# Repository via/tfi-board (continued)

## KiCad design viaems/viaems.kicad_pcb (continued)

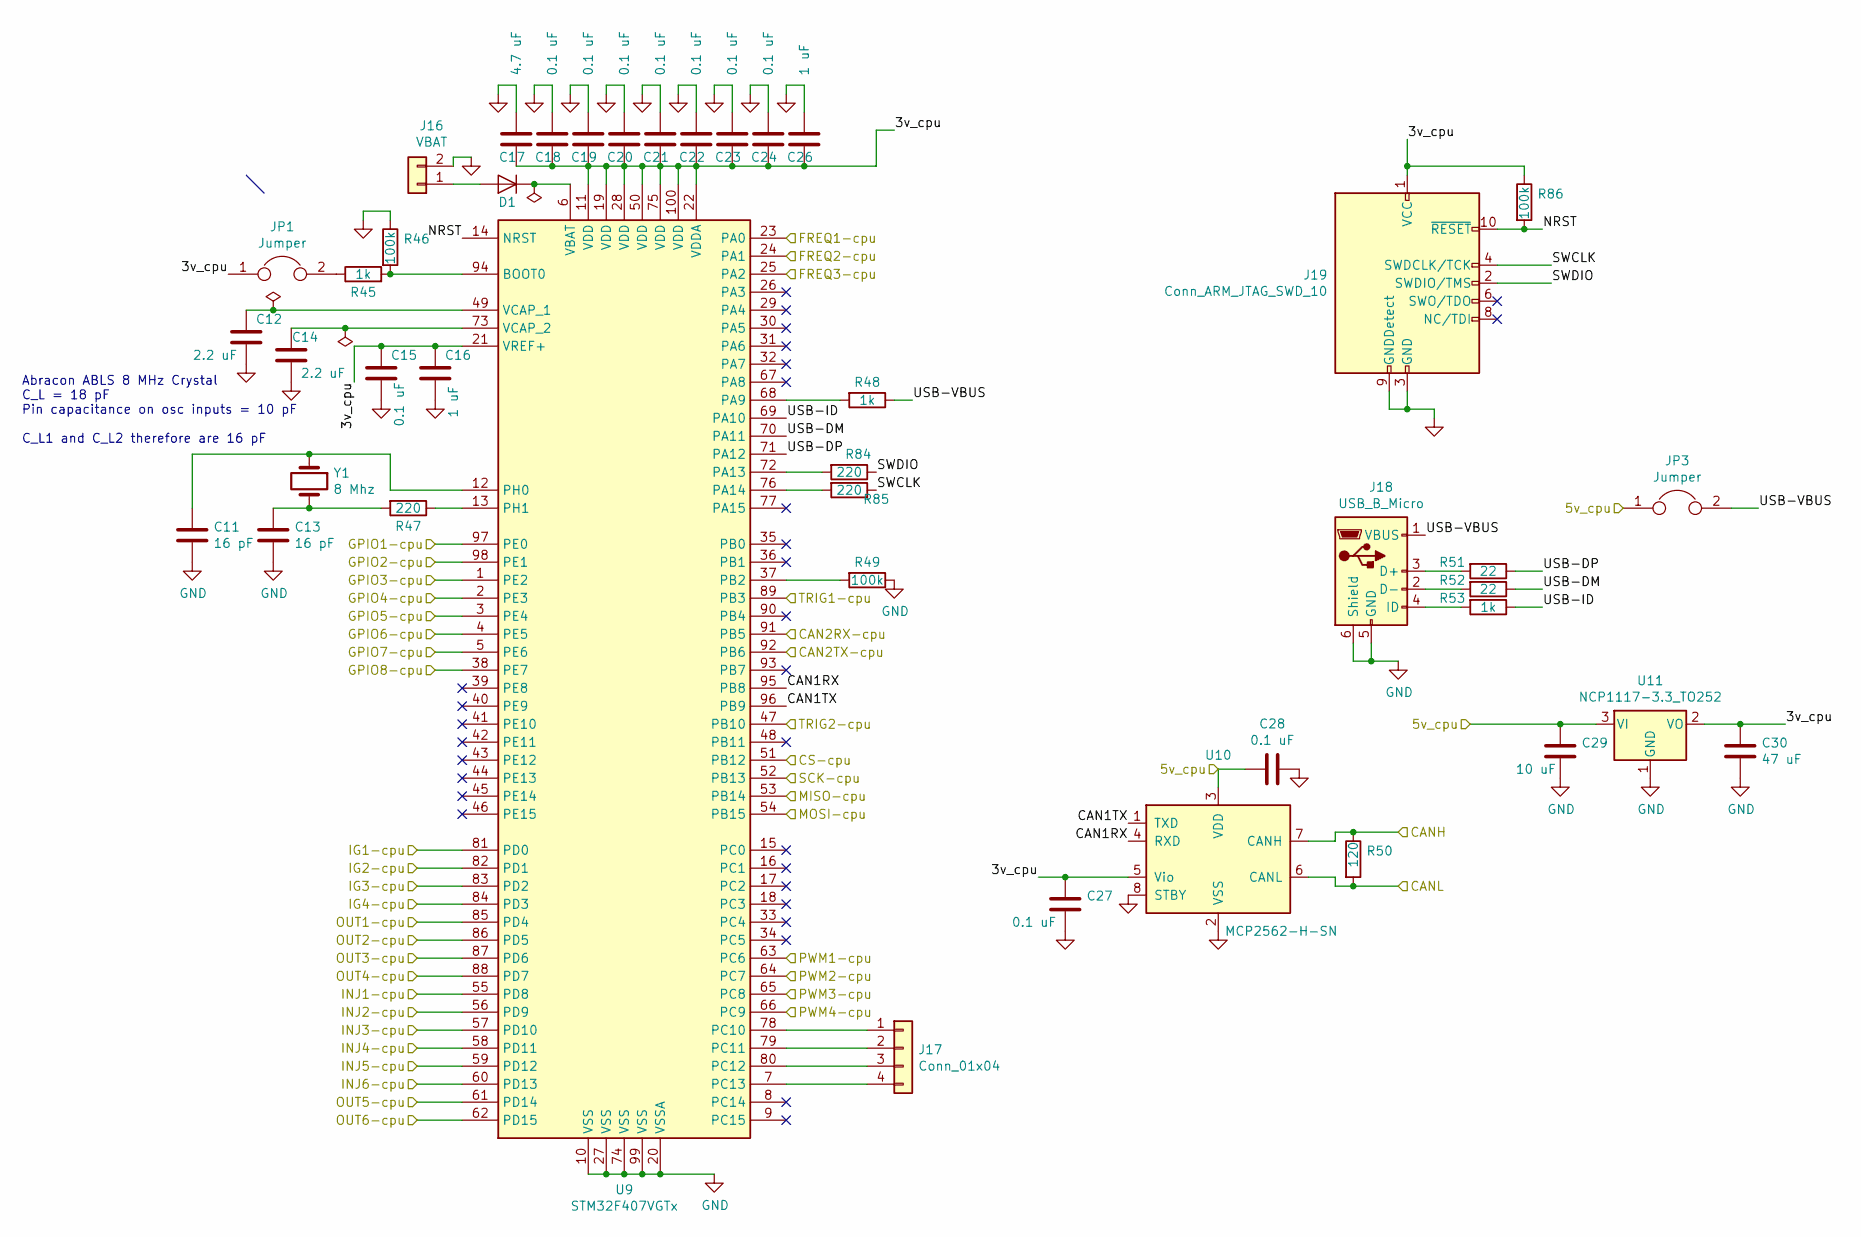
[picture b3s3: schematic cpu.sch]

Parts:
C11, C13: 16 pF; C_0805_2012Metric_Pad1.15x1.40mm_HandSolder; Digikey-Part 311-4228-1-ND
C12, C14: 2.2 uF; C_0805_2012Metric_Pad1.15x1.40mm_HandSolder; Digikey-Part 1276-1188-1-ND
C15, C18, C19, C20, C21, C22, C23, C24, C27, C28: 0.1 uF; C_0805_2012Metric_Pad1.15x1.40mm_HandSolder; Digikey-Part 478-10836-1-ND
C16, C26: 1 uF; C_0805_2012Metric_Pad1.15x1.40mm_HandSolder; Digikey-Part 1276-1066-1-ND
C17: 4.7 uF; C_0805_2012Metric_Pad1.15x1.40mm_HandSolder; Digikey-Part 445-14527-1-ND
C29: 10 uF; C_0805_2012Metric_Pad1.15x1.40mm_HandSolder; Digikey-Part 587-3417-1-ND
C30: 47 uF; C_1206_3216Metric_Pad1.42x1.75mm_HandSolder; Digikey-Part 478-9009-1-ND
D1: D; D_0805_2012Metric_Pad1.15x1.40mm_HandSolder; Digikey-Part 478-7802-1-ND
J16: VBAT; PinHeader_1x02_P2.54mm_Vertical; Digikey-Part 952-2262-ND
J17: Conn_01x04; PinHeader_1x04_P2.54mm_Vertical; Digikey-Part 732-5317-ND
J18: USB_B_Micro; USB_Micro-B_Amphenol_10103594-0001LF_Horizontal; Digikey-Part 609-4050-1-ND
J19: Conn_ARM_JTAG_SWD_10; PinHeader_2x05_P1.27mm_Vertical_SMD; Digikey-Part SAM9438-ND
JP1, JP3: Jumper; PinHeader_1x02_P2.54mm_Vertical; Digikey-Part 952-2262-ND
R45, R48, R53: 1k; R_0805_2012Metric_Pad1.15x1.40mm_HandSolder; Digikey-Part RNCP0805FTD1K00CT-ND
R46, R49, R86: 100k; R_0805_2012Metric_Pad1.15x1.40mm_HandSolder; Digikey-Part P100KDACT-ND
R47, R84, R85: 220; R_0805_2012Metric_Pad1.15x1.40mm_HandSolder; Digikey-Part A129741CT-ND
R50: 120; R_0805_2012Metric_Pad1.15x1.40mm_HandSolder; Digikey-Part P16874CT-ND
R51, R52: 22; R_0805_2012Metric_Pad1.15x1.40mm_HandSolder; Digikey-Part A130124CT-ND
U9: STM32F407VGTx; LQFP-100_14x14mm_P0.5mm; Digikey-Part 497-17438-ND
U10: MCP2562-H-SN; SOIC-8_3.9x4.9mm_P1.27mm; Digikey-Part MCP2562-H/SN
U11: NCP1117-3.3_TO252; TO-252-2; Digikey-Part NCP1117DT33T5GOSCT-ND
Y1: 8 Mhz; Crystal_HC49-U_Vertical; Digikey-Part 535-10212-1-ND

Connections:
5v_cpu: C28.2, C29.1, JP3.1, U10.3 (VDD), U11.3 (VI); also elsewhere on the board
/CANH: R50.1, U10.7 (CANH); also elsewhere on the board
/CANL: R50.2, U10.6 (CANL); also elsewhere on the board
/Cpu/3v_cpu: C15.1, C16.1, C17.2, C18.2, C19.2, C20.2, C21.2, C22.2, C23.2, C24.2, C26.2, C27.1, C30.1, J19.1 (VCC), JP1.1, R86.1, U9.11 (VDD), U9.19 (VDD), U9.21 (VREF+), U9.22 (VDDA), U9.28 (VDD), U9.50 (VDD), U9.75 (VDD), U9.100 (VDD), U10.5 (Vio), U11.2 (VO)
/Cpu/CAN1RX: U9.95 (PB8), U10.4 (RXD)
/Cpu/CAN1TX: U9.96 (PB9), U10.1 (TXD)
/Cpu/CAN2RX-cpu: U9.91 (PB5); also elsewhere on the board
/Cpu/CAN2TX-cpu: U9.92 (PB6); also elsewhere on the board
/Cpu/FREQ1-cpu: U9.23 (PA0); also elsewhere on the board
/Cpu/FREQ2-cpu: U9.24 (PA1); also elsewhere on the board
/Cpu/FREQ3-cpu: U9.25 (PA2); also elsewhere on the board
/Cpu/GPIO1-cpu: U9.97 (PE0); also elsewhere on the board
/Cpu/GPIO2-cpu: U9.98 (PE1); also elsewhere on the board
/Cpu/GPIO3-cpu: U9.1 (PE2); also elsewhere on the board
/Cpu/GPIO4-cpu: U9.2 (PE3); also elsewhere on the board
/Cpu/GPIO5-cpu: U9.3 (PE4); also elsewhere on the board
/Cpu/GPIO6-cpu: U9.4 (PE5); also elsewhere on the board
/Cpu/GPIO7-cpu: U9.5 (PE6); also elsewhere on the board
/Cpu/GPIO8-cpu: U9.38 (PE7); also elsewhere on the board
/Cpu/INJ3-cpu: U9.57 (PD10); also elsewhere on the board
/Cpu/INJ4-cpu: U9.58 (PD11); also elsewhere on the board
/Cpu/INJ5-cpu: U9.59 (PD12); also elsewhere on the board
/Cpu/INJ6-cpu: U9.60 (PD13); also elsewhere on the board
/Cpu/NRST: J19.10 (~RESET~), R86.2, U9.14 (NRST)
/Cpu/OUT1-cpu: U9.85 (PD4); also elsewhere on the board
/Cpu/OUT2-cpu: U9.86 (PD5); also elsewhere on the board
/Cpu/OUT3-cpu: U9.87 (PD6); also elsewhere on the board
/Cpu/OUT4-cpu: U9.88 (PD7); also elsewhere on the board
/Cpu/OUT5-cpu: U9.61 (PD14); also elsewhere on the board
/Cpu/OUT6-cpu: U9.62 (PD15); also elsewhere on the board
/Cpu/PWM1-cpu: U9.63 (PC6); also elsewhere on the board
/Cpu/PWM2-cpu: U9.64 (PC7); also elsewhere on the board
/Cpu/PWM3-cpu: U9.65 (PC8); also elsewhere on the board
/Cpu/PWM4-cpu: U9.66 (PC9); also elsewhere on the board
/Cpu/SCK-cpu: U9.52 (PB13); also elsewhere on the board
/Cpu/SWCLK: J19.4 (SWDCLK/TCK), R85.1
/Cpu/SWDIO: J19.2 (SWDIO/TMS), R84.1
/Cpu/TRIG1-cpu: U9.89 (PB3); also elsewhere on the board
/Cpu/TRIG2-cpu: U9.47 (PB10); also elsewhere on the board
/Cpu/USB-DM: R52.1, U9.70 (PA11)
/Cpu/USB-DP: R51.1, U9.71 (PA12)
/Cpu/USB-ID: R53.1, U9.69 (PA10)
/Cpu/USB-VBUS: J18.1 (VBUS), JP3.2, R48.1
/Inputs/CS: U9.51 (PB12); also elsewhere on the board
/Inputs/MISO: U9.53 (PB14); also elsewhere on the board
/Inputs/MOSI: U9.54 (PB15); also elsewhere on the board
/Outputs/IG1: U9.81 (PD0); also elsewhere on the board
/Outputs/IG2: U9.82 (PD1); also elsewhere on the board
/Outputs/IG3: U9.83 (PD2); also elsewhere on the board
/Outputs/IG4: U9.84 (PD3); also elsewhere on the board
/Outputs/INJ1: U9.55 (PD8); also elsewhere on the board
/Outputs/INJ2: U9.56 (PD9); also elsewhere on the board
GND: C11.2, C12.2, C13.2, C14.2, C15.2, C16.2, C17.1, C18.1, C19.1, C20.1, C21.1, C22.1, C23.1, C24.1, C26.1, C27.2, C28.1, C29.2, C30.2, J16.2, J18.5 (GND), J18.6 (Shield), J19.3 (GND), J19.5 (GND), J19.9 (GNDDetect), R46.1, R49.1, U9.10 (VSS), U9.20 (VSSA), U9.27 (VSS), U9.74 (VSS), U9.99 (VSS), U10.2 (VSS), U10.8 (STBY), U11.1 (GND); also elsewhere on the board
unnamed: C11.1, U9.12 (PH0), Y1.1
unnamed: C12.1, U9.49 (VCAP_1)
unnamed: C13.1, R47.2, Y1.2
unnamed: C14.1, U9.73 (VCAP_2)
unnamed: D1.1 (K), U9.6 (VBAT)
unnamed: D1.2 (A), J16.1
unnamed: J17.1, U9.78 (PC10)
unnamed: J17.2, U9.79 (PC11)
unnamed: J17.3, U9.80 (PC12)
unnamed: J17.4, U9.7 (PC13)
unnamed: J18.2 (D-), R52.2
unnamed: J18.3 (D+), R51.2
unnamed: J18.4 (ID), R53.2
unnamed: JP1.2, R45.1
unnamed: R45.2, R46.2, U9.94 (BOOT0)
unnamed: R47.1, U9.13 (PH1)
unnamed: R48.2, U9.68 (PA9)
unnamed: R49.2, U9.37 (PB2)
unnamed: R84.2, U9.72 (PA13)
unnamed: R85.2, U9.76 (PA14)

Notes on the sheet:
Abracon ABLS 8 MHz Crystal C_L = 18 pF Pin capacitance on osc inputs = 10 pF C_L1 and C_L2 therefore are 16 pF

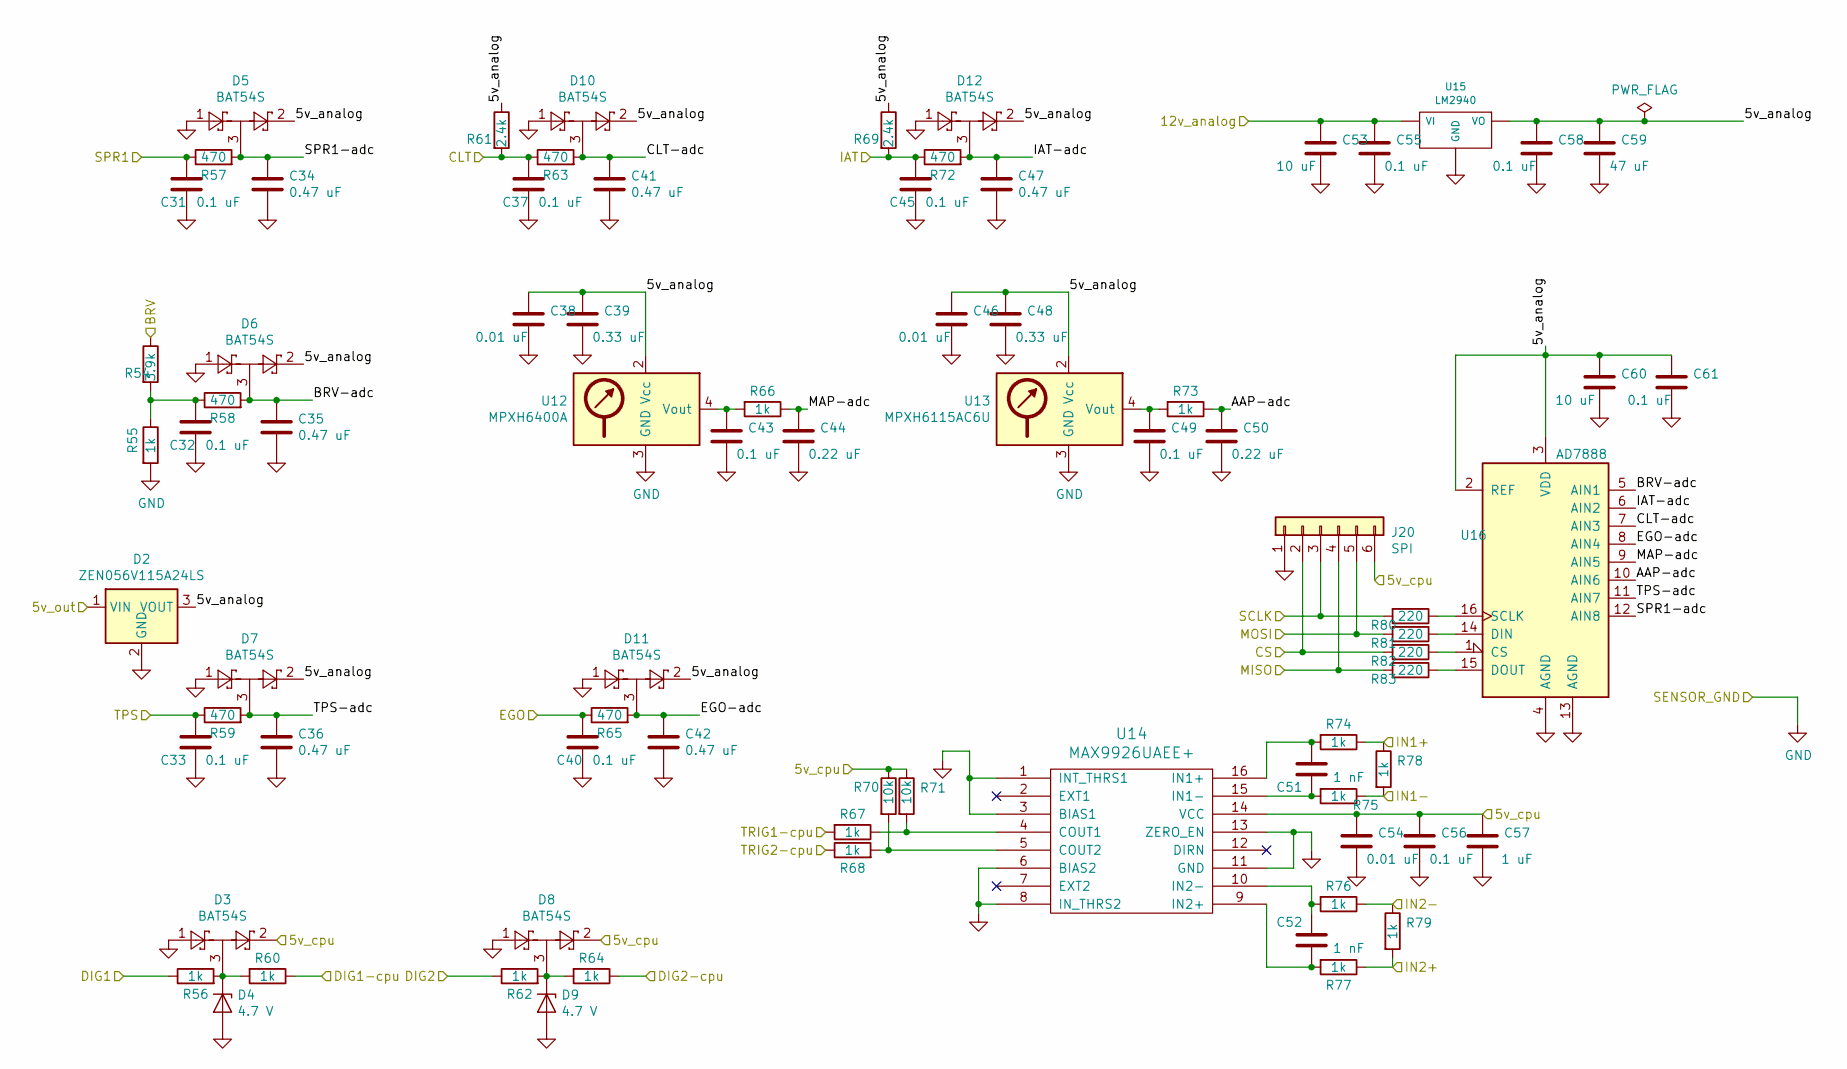
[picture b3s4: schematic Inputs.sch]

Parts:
C31, C32, C33, C37, C40, C45, C49, C55, C56, C58, C61: 0.1 uF; C_0805_2012Metric_Pad1.15x1.40mm_HandSolder; Digikey-Part 478-10836-1-ND
C34, C35, C36, C41, C42, C47: 0.47 uF; C_0805_2012Metric_Pad1.15x1.40mm_HandSolder; Digikey-Part 1276-6851-1-ND
C38, C46, C54: 0.01 uF; C_0805_2012Metric_Pad1.15x1.40mm_HandSolder; Digikey-Part 1276-1015-1-ND
C39, C48: 0.33 uF; C_0805_2012Metric_Pad1.15x1.40mm_HandSolder; Digikey-Part 1276-1123-1-ND
C43: 0.1 uF; C_0805_2012Metric_Pad1.15x1.40mm_HandSolder; Digikey-Part 1276-1015-1-ND
C44, C50: 0.22 uF; C_0805_2012Metric_Pad1.15x1.40mm_HandSolder; Digikey-Part 1276-1093-1-ND
C51, C52: 1 nF; C_0805_2012Metric_Pad1.15x1.40mm_HandSolder; Digikey-Part 399-1147-1-ND
C53: 10 uF; C_1206_3216Metric_Pad1.42x1.75mm_HandSolder; Digikey-Part 445-8034-1-ND
C57: 1 uF; C_0805_2012Metric_Pad1.15x1.40mm_HandSolder; Digikey-Part 1276-1066-1-ND
C59: 47 uF; C_1206_3216Metric_Pad1.42x1.75mm_HandSolder; Digikey-Part 478-9009-1-ND
C60: 10 uF; C_0805_2012Metric_Pad1.15x1.40mm_HandSolder; Digikey-Part 587-3417-1-ND
D2: ZEN056V115A24LS; Littelfuse_PolyZen-LS; Digikey-Part ZEN056V115A24LSCT-ND
D3, D5, D6, D7, D8, D10, D11, D12: BAT54S; SOT-23_Handsoldering; Digikey-Part BAT54SLT1GOSCT-ND
D4: 4.7 V; D_0603_1608Metric_Pad1.05x0.95mm_HandSolder
D9: 4.7 V; D_0805_2012Metric_Pad1.15x1.40mm_HandSolder
J20: SPI; PinHeader_1x06_P2.54mm_Vertical; Digikey-Part 732-5319-ND
R54: 3.9k; R_0805_2012Metric_Pad1.15x1.40mm_HandSolder; Digikey-Part P3.9KDACT-ND
R55: 1k; R_0805_2012Metric_Pad1.15x1.40mm_HandSolder; Digikey-Part P1.0KDACT-ND
R56, R60, R62, R64, R66, R67, R68, R73, R74, R75, R76, R77: 1k; R_0805_2012Metric_Pad1.15x1.40mm_HandSolder; Digikey-Part RNCP0805FTD1K00CT-ND
R57, R58, R59, R63, R65, R72: 470; R_0805_2012Metric_Pad1.15x1.40mm_HandSolder; Digikey-Part 311-470CRCT-ND
R61, R69: 2.4k; R_0805_2012Metric_Pad1.15x1.40mm_HandSolder; Digikey-Part P2.4KDACT-ND
R70, R71: 10k; R_0805_2012Metric_Pad1.15x1.40mm_HandSolder; Digikey-Part RNCF0805DTE10K0CT-ND
R78, R79: 1k; R_Axial_DIN0207_L6.3mm_D2.5mm_P2.54mm_Vertical; Digikey-Part PPC1.0KW-1CT-ND
R80, R81, R82, R83: 220; R_0805_2012Metric_Pad1.15x1.40mm_HandSolder; Digikey-Part A129741CT-ND
U12: MPXH6400A; Freescale_98ARH99089A; Digikey-Part MPXH6400AC6T1CT-ND
U13: MPXH6115AC6U; Freescale_98ARH99089A; Digikey-Part MPXH6115AC6U-ND
U14: MAX9926UAEE+; QSOP-16_3.9x4.9mm_P0.635mm; Digikey-Part MAX9926UAEE+TCT-ND
U15: LM2940; TO-220-3_Horizontal_TabDown; Digikey-Part LM2940T-5.0/NOPB-ND
U16: AD7888; SOIC-16_3.9x9.9mm_P1.27mm; Digikey-Part AD7888ARZ-REEL7CT-ND

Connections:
5v_cpu: C54.1, C56.1, C57.1, D3.2, D8.2, J20.6, R70.1, R71.1, U14.14 (VCC); also elsewhere on the board
/Cpu/SCK-cpu: J20.3, R80.2; also elsewhere on the board
/Cpu/TRIG1-cpu: R67.2; also elsewhere on the board
/Cpu/TRIG2-cpu: R68.1; also elsewhere on the board
/Inputs/5v_analog: C38.1, C39.1, C46.1, C48.1, C58.1, C59.1, C60.1, C61.1, D2.3 (VOUT), D5.2, D6.2, D7.2, D10.2, D11.2, D12.2, R61.1, R69.1, U12.2 (Vcc), U13.2 (Vcc), U15.3 (VO), U16.2 (REF), U16.3 (VDD)
/Inputs/5v_out: D2.1 (VIN); also elsewhere on the board
/Inputs/12v_analog: C53.1, C55.1, U15.1 (VI); also elsewhere on the board
/Inputs/AAP-adc: C50.1, R73.1, U16.10 (AIN6)
/Inputs/BRV: R54.1; also elsewhere on the board
/Inputs/BRV-adc: C35.1, D6.3, R58.2, U16.5 (AIN1)
/Inputs/CLT: C37.1, R61.2, R63.1; also elsewhere on the board
/Inputs/CLT-adc: C41.1, D10.3, R63.2, U16.7 (AIN3)
/Inputs/CS: J20.2, R82.2; also elsewhere on the board
/Inputs/DIG1: R56.1; also elsewhere on the board
/Inputs/DIG1-cpu: R60.1; also elsewhere on the board
/Inputs/DIG2: R62.1; also elsewhere on the board
/Inputs/DIG2-cpu: R64.1; also elsewhere on the board
/Inputs/EGO: C40.1, R65.1; also elsewhere on the board
/Inputs/EGO-adc: C42.1, D11.3, R65.2, U16.8 (AIN4)
/Inputs/IAT: C45.1, R69.2, R72.1; also elsewhere on the board
/Inputs/IAT-adc: C47.1, D12.3, R72.2, U16.6 (AIN2)
/Inputs/IN1+: R74.1, R78.1; also elsewhere on the board
/Inputs/IN1-: R75.1, R78.2; also elsewhere on the board
/Inputs/IN2+: R77.1, R79.2; also elsewhere on the board
/Inputs/IN2-: R76.1, R79.1; also elsewhere on the board
/Inputs/MAP-adc: C44.1, R66.1, U16.9 (AIN5)
/Inputs/MISO: J20.4, R83.2; also elsewhere on the board
/Inputs/MOSI: J20.5, R81.2; also elsewhere on the board
/Inputs/SPR1: C31.1, R57.1; also elsewhere on the board
/Inputs/SPR1-adc: C34.1, D5.3, R57.2, U16.12 (AIN8)
/Inputs/TPS: C33.1, R59.1; also elsewhere on the board
/Inputs/TPS-adc: C36.1, D7.3, R59.2, U16.11 (AIN7)
GND: C31.2, C32.2, C33.2, C34.2, C35.2, C36.2, C37.2, C38.2, C39.2, C40.2, C41.2, C42.2, C43.2, C44.2, C45.2, C46.2, C47.2, C48.2, C49.2, C50.2, C53.2, C54.2, C55.2, C56.2, C57.2, C58.2, C59.2, C60.2, C61.2, D2.2 (GND), D3.1, D4.2 (A), D5.1, D6.1, D7.1, D8.1, D9.2 (A), D10.1, D11.1, D12.1, J20.1, R55.2, U12.3 (GND), U13.3 (GND), U14.1 (INT_THRS1), U14.3 (BIAS1), U14.6 (BIAS2), U14.8 (IN_THRS2), U14.11 (GND), U14.13 (ZERO_EN), U15.2 (GND), U16.4 (AGND), U16.13 (AGND); also elsewhere on the board
unnamed: C32.1, R54.2, R55.1, R58.1
unnamed: C43.1, R66.2, U12.4 (Vout)
unnamed: C49.1, R73.2, U13.4 (Vout)
unnamed: C51.1, R74.2, U14.16 (IN1+)
unnamed: C51.2, R75.2, U14.15 (IN1-)
unnamed: C52.1, R76.2, U14.10 (IN2-)
unnamed: C52.2, R77.2, U14.9 (IN2+)
unnamed: D3.3, D4.1 (K), R56.2, R60.2
unnamed: D8.3, D9.1 (K), R62.2, R64.2
unnamed: R67.1, R71.2, U14.4 (COUT1)
unnamed: R68.2, R70.2, U14.5 (COUT2)
unnamed: R80.1, U16.16 (SCLK)
unnamed: R81.1, U16.14 (DIN)
unnamed: R82.1, U16.1 (CS)
unnamed: R83.1, U16.15 (DOUT)

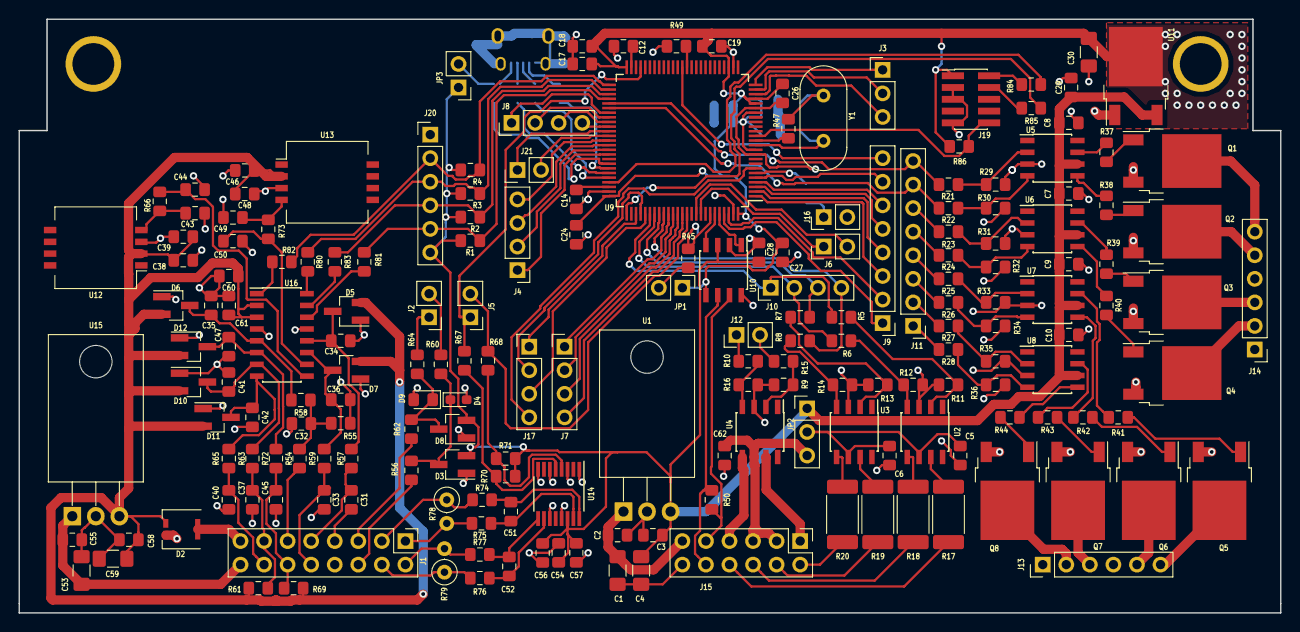
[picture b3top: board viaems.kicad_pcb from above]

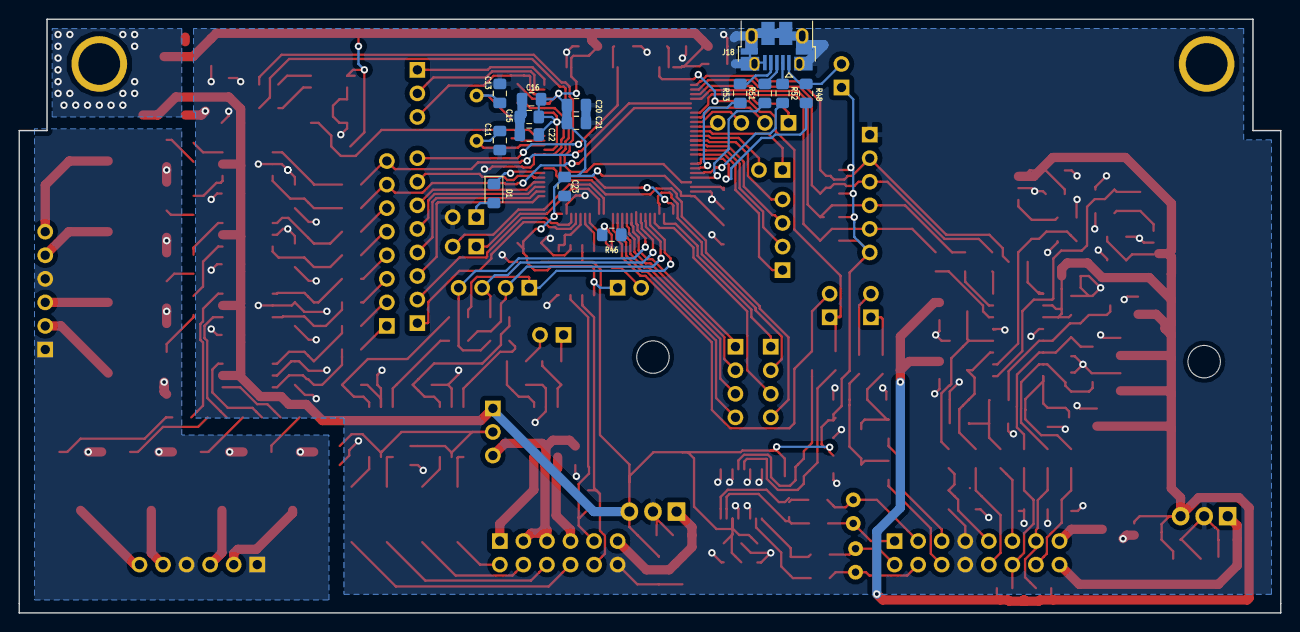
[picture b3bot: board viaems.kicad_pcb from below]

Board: 2 copper layers, 136.0 x 64.0 mm, 208 parts (15 on the bottom side), 173 nets.

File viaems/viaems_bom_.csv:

Component,Description,Part,References,Value,Footprint,Quantity Per PCB,Datasheet,Digikey-Part,Notes
1,Unpolarized capacitor,C,C38 C46 C54,0.01 uF,C_0805_2012Metric_Pad1.15x1.40mm_HandSolder,3,~,1276-1015-1-ND,
2,Unpolarized capacitor,C,C2 C3 C15 C18 C19 C20 C21 C22 C23 C24 C27 C28 C31 C32 C33 C37 C40 C45 C49 C55 C56 C58 C61,0.1 uF,C_0805_2012Metric_Pad1.15x1.40mm_HandSolder,23,~,478-10836-1-ND,35V
3,Unpolarized capacitor,C,C43,0.1 uF,C_0805_2012Metric_Pad1.15x1.40mm_HandSolder,1,~,1276-1015-1-ND,
4,Unpolarized capacitor,C,C44 C50,0.22 uF,C_0805_2012Metric_Pad1.15x1.40mm_HandSolder,2,~,1276-1093-1-ND,
5,Unpolarized capacitor,C,C39 C48,0.33 uF,C_0805_2012Metric_Pad1.15x1.40mm_HandSolder,2,~,1276-1123-1-ND,
6,Unpolarized capacitor,C,C34 C35 C36 C41 C42 C47,0.47 uF,C_0805_2012Metric_Pad1.15x1.40mm_HandSolder,6,~,1276-6851-1-ND,
7,Unpolarized capacitor,C,C51 C52,1 nF,C_0805_2012Metric_Pad1.15x1.40mm_HandSolder,2,~,399-1147-1-ND,
8,Unpolarized capacitor,C,C16 C26 C57,1 uF,C_0805_2012Metric_Pad1.15x1.40mm_HandSolder,3,~,1276-1066-1-ND,
9,Unpolarized capacitor,C,C1 C53,10 uF,C_1206_3216Metric_Pad1.42x1.75mm_HandSolder,2,~,445-8034-1-ND,35V
10,Unpolarized capacitor,C,C29 C60,10 uF,C_0805_2012Metric_Pad1.15x1.40mm_HandSolder,2,~,587-3417-1-ND,
11,Unpolarized capacitor,C,C11 C13,16 pF,C_0805_2012Metric_Pad1.15x1.40mm_HandSolder,2,~,311-4228-1-ND,
12,Unpolarized capacitor,C,C5 C6 C7 C8 C9 C10 C62,1uF,C_0805_2012Metric_Pad1.15x1.40mm_HandSolder,7,~,1276-1029-1-ND,35V
13,Unpolarized capacitor,C,C12 C14,2.2 uF,C_0805_2012Metric_Pad1.15x1.40mm_HandSolder,2,~,1276-1188-1-ND,ESR < 2.2 ohm ESR < 2.2 ohms
14,Unpolarized capacitor,C,C17,4.7 uF,C_0805_2012Metric_Pad1.15x1.40mm_HandSolder,1,~,445-14527-1-ND,
15,Unpolarized capacitor,C,C4 C30 C59,47 uF,C_1206_3216Metric_Pad1.42x1.75mm_HandSolder,3,~,478-9009-1-ND,Tantalum 33 mOhm < ESR < 2.2 ohm
16,Zener diode,D_Zener,D4,4.7 V,D_0603_1608Metric_Pad1.05x0.95mm_HandSolder,1,~,,
17,Zener diode,D_Zener,D9,4.7 V,D_0805_2012Metric_Pad1.15x1.40mm_HandSolder,1,~,,
18,schottky barrier diode,BAT54S,D3 D5 D6 D7 D8 D10 D11 D12,BAT54S,SOT-23_Handsoldering,8,https://www.diodes.com/assets/Datasheets/ds11005.pdf,BAT54SLT1GOSCT-ND,
19,Diode,D,D1,D,D_0805_2012Metric_Pad1.15x1.40mm_HandSolder,1,~,478-7802-1-ND,
20,"Polymer Protected Zener Diode, 5.6V, 1.15A, 24V, LS",ZEN056V115A24LS,D2,ZEN056V115A24LS,Littelfuse_PolyZen-LS,1,http://m.littelfuse.com/~/media/electronics/datasheets/polyz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,ZEN056V115A24LSCT-ND,
21,"Generic connector, single row, 01x02, script generated (kicad-library-utils/schlib/autogen/connector/)",Conn_01x02,J2 J5 J6 J12 J16 J21,Conn_01x02,PinHeader_1x02_P2.54mm_Vertical,6,~,952-2262-ND,
22,"Generic connector, single row, 01x03, script generated (kicad-library-utils/schlib/autogen/connector/)",Conn_01x03,J3,Conn_01x03,PinHeader_1x03_P2.54mm_Vertical,1,~,732-5316-ND,
23,"Generic connector, single row, 01x04, script generated (kicad-library-utils/schlib/autogen/connector/)",Conn_01x04,J4 J7 J8 J10 J17,Conn_01x04,PinHeader_1x04_P2.54mm_Vertical,5,~,732-5317-ND,
24,"Generic connector, single row, 01x06, script generated (kicad-library-utils/schlib/autogen/connector/)",Conn_01x06,J13 J14 J20,Conn_01x06,PinHeader_1x06_P2.54mm_Vertical,3,~,732-5319-ND,
25,"Generic connector, single row, 01x08, script generated (kicad-library-utils/schlib/autogen/connector/)",Conn_01x08,J9 J11,Conn_01x08,PinHeader_1x08_P2.54mm_Vertical,2,~,732-5321-ND,
26,"Generic connector, double row, 02x06, odd/even pin numbering scheme (row 1 odd numbers, row 2 even numbers), script generated (kicad-library-utils/schlib/autogen/connector/)",Conn_02x06_Odd_Even,J15,Conn_02x06_Odd_Even,PinHeader_2x06_P2.54mm_Vertical,1,~,732-5297-ND,
27,"Generic connector, double row, 02x08, counter clockwise pin numbering scheme (similar to DIP packge numbering), script generated (kicad-library-utils/schlib/autogen/connector/)",Conn_02x08_Counter_Clockwise,J1,Conn_02x08_Counter_Clockwise,PinHeader_2x08_P2.54mm_Vertical,1,~,609-3220-ND,
28,"Cortex Debug Connector, standard ARM Cortex-M SWD and JTAG interface",Conn_ARM_JTAG_SWD_10,J19,Conn_ARM_JTAG_SWD_10,PinHeader_2x05_P1.27mm_Vertical_SMD,1,http://infocenter.arm.com/help/topic/com.arm.doc.faqs/attach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,SAM9438-ND,
29,USB Micro Type B connector,USB_B_Micro,J18,USB_B_Micro,USB_Micro-B_Amphenol_10103594-0001LF_Horizontal,1,~,609-4050-1-ND,
30,"Jumper, normally closed",Jumper,JP1 JP3,Jumper,PinHeader_1x02_P2.54mm_Vertical,2,~,952-2262-ND,
31,"Dual jumper, normally closed",Jumper_NC_Dual,JP2,Jumper_NC_Dual,PinHeader_1x03_P2.54mm_Vertical,1,~,732-5316-ND,
32,"N-MOSFET transistor, gate/drain/source",Q_NMOS_GDS,Q1 Q2 Q3 Q4 Q5 Q6 Q7 Q8,VND7NV04,TO-252-2,8,~,497-11707-1-ND,
33,Resistor,R,R1 R2 R3 R4 R11 R12 R13 R14 R15 R16 R29 R30 R31 R32 R33 R34 R35 R36 R46 R49 R86,100k,R_0805_2012Metric_Pad1.15x1.40mm_HandSolder,21,~,P100KDACT-ND,
34,Resistor,R,R70 R71,10k,R_0805_2012Metric_Pad1.15x1.40mm_HandSolder,2,~,RNCF0805DTE10K0CT-ND,
35,Resistor,R,R50,120,R_0805_2012Metric_Pad1.15x1.40mm_HandSolder,1,~,P16874CT-ND,
36,Resistor,R,R17 R18 R19 R20,150,R_2512_6332Metric_Pad1.52x3.35mm_HandSolder,4,~,541-150XCT-ND,1W
37,Resistor,R,R37 R38 R39 R40 R41 R42 R43 R44,150,R_0805_2012Metric_Pad1.15x1.40mm_HandSolder,8,~,RNCP0805FTD150RCT-ND,
38,Resistor,R,R5 R6 R7 R8 R9 R10 R21 R22 R23 R24 R25 R26 R27 R28 R45 R48 R53 R56 R60 R62 R64 R66 R67 R68 R73 R74 R75 R76 R77,1k,R_0805_2012Metric_Pad1.15x1.40mm_HandSolder,29,~,RNCP0805FTD1K00CT-ND,
39,Resistor,R,R55,1k,R_0805_2012Metric_Pad1.15x1.40mm_HandSolder,1,~,P1.0KDACT-ND,0.1%
40,Resistor,R,R78 R79,1k,R_Axial_DIN0207_L6.3mm_D2.5mm_P2.54mm_Vertical,2,~,PPC1.0KW-1CT-ND,1W
41,Resistor,R,R61 R69,2.4k,R_0805_2012Metric_Pad1.15x1.40mm_HandSolder,2,~,P2.4KDACT-ND,
42,Resistor,R,R51 R52,22,R_0805_2012Metric_Pad1.15x1.40mm_HandSolder,2,~,A130124CT-ND,
43,Resistor,R,R47 R80 R81 R82 R83 R84 R85,220,R_0805_2012Metric_Pad1.15x1.40mm_HandSolder,7,~,A129741CT-ND,
44,Resistor,R,R54,3.9k,R_0805_2012Metric_Pad1.15x1.40mm_HandSolder,1,~,P3.9KDACT-ND,0.1%
45,Resistor,R,R57 R58 R59 R63 R65 R72,470,R_0805_2012Metric_Pad1.15x1.40mm_HandSolder,6,~,311-470CRCT-ND,
46,,AD7888,U16,AD7888,SOIC-16_3.9x9.9mm_P1.27mm,1,,AD7888ARZ-REEL7CT-ND,
47,,LM2940,U1 U15,LM2940,TO-220-3_Horizontal_TabDown,2,,LM2940T-5.0/NOPB-ND,
48,,MAX9926UAEE+,U14,MAX9926UAEE+,QSOP-16_3.9x4.9mm_P0.635mm,1,,MAX9926UAEE+TCT-ND,
49,"High-Speed CAN Transceiver, 1Mbps, 5V supply, Vio pin, -40C to +150C, SOIC8 package",MCP2562-H-SN,U10,MCP2562-H-SN,SOIC-8_3.9x4.9mm_P1.27mm,1,http://ww1.microchip.com/downloads/en/DeviceDoc/25167A.pdf,MCP2562-H/SN,
50,"Absolute pressure sensor, 15 to 115kPa, analog output, integrated signal conditioning, temperature compensated, SO package",MPXA6115A,U13,MPXH6115AC6U,Freescale_98ARH99089A,1,http://www.nxp.com/files/sensors/doc/data_sheet/MPXA6115A.pdf,MPXH6115AC6U-ND,
51,"Absolute pressure sensor, 15 to 115kPa, analog output, integrated signal conditioning, temperature compensated, SO package",MPXA6115A,U12,MPXH6400A,Freescale_98ARH99089A,1,http://www.nxp.com/files/sensors/doc/data_sheet/MPXA6115A.pdf,MPXH6400AC6T1CT-ND,
52,"1A Low drop-out regulator, Fixed Output 3.3V, TO-252 (DPAK)",NCP1117-3.3_TO252,U11,NCP1117-3.3_TO252,TO-252-2,1,http://www.onsemi.com/pub_link/Collateral/NCP1117-D.PDF,NCP1117DT33T5GOSCT-ND,
53,"ARM Cortex-M4 MCU, 1024KB flash, 128KB RAM, 168MHz, 1.8-3.6V, 82 GPIO, LQFP-100",STM32F407VGTx,U9,STM32F407VGTx,LQFP-100_14x14mm_P0.5mm,1,http://www.st.com/st-web-ui/static/active/en/resource/techni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,497-17438-ND,
54,,TC442xA,U2 U3 U4 U5 U6 U7 U8,TC442xA,SOIC-8_3.9x4.9mm_P1.27mm,7,,TC4427EOA713CT-ND,
55,Two pin crystal,Crystal,Y1,8 Mhz,Crystal_HC49-U_Vertical,1,~,535-10212-1-ND,





Component Groups:,55
Component Count:,208
Fitted Components:,208
Number of PCBs:,1
Total components:,208
Schematic Version:,
Schematic Date:,
BoM Date:,Sun 05 May 2019 05:27:50 PM EDT
Schematic Source:,/home/via/dev/tfi-board/viaems/viaems.sch
KiCad Version:,Eeschema 5.0.2+dfsg1-1

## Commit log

2018-03-02 Gitignore
2018-03-02 Add analog and io board
2018-03-02 Add parts cache files
2018-03-02 Add Readme
2018-03-02 Add plots for rc1
2018-03-05 Add notes and ratings
2018-03-05 Add BOMs
2018-12-01 Add caches
2018-12-01 First draft of viaems
2018-12-08 More progress. Calling schematic complete, board partially routed
2018-12-13 More routing
2019-04-25 Finished routing
2019-06-15 Misc fixes
2019-06-15 Add bom
2021-11-28 Various updates to io board: - Add trigger inputs - Switch to 3v logic fets - switch to SMT components
2021-11-29 fixes
2021-11-30 Switch to a gate driver and normal power mosfets
2021-12-04 fixups
2021-12-04 Post-pcb process unfuckening of basic missing traces
    like a dumbass
2022-06-15 Add license
